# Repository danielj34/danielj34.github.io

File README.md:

# danielj34.github.io
Daniel Joseph — engineering portfolio

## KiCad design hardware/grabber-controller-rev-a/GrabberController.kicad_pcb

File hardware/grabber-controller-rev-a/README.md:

# Grabber Controller - Revision A

ESP32 motor-control carrier PCB design, Revision A. November 12, 2026.

This design develops the ESP32 / dual-motor-controller concept for Daniel Joseph's assistive-grabber portfolio. The team's completed mechanical prototype used a switch-based control circuit. The files here document the PCB design.

## Design

- 111.76 x 86.36 mm two-layer carrier PCB, nominal 1.6 mm FR-4 / 1 oz copper.
- U1 is a socketed Espressif ESP32-DevKitC V4 with a WROOM module. The two 19-pin rows are 25.40 mm apart at 2.54 mm pin pitch. WROVER variants are unsuitable for the selected GPIO16/17 assignment.
- U2 is a socket for the SparkFun ROB-14450 dual TB6612FNG driver module, two 8-pin rows 15.24 mm apart at 2.54 mm pitch. The driver IC is on that module, not directly on this carrier.
- ESP32 logic power comes only through its own USB connector. The carrier's J1 input feeds only the motor rail. The two rails share ground.
- J1 is a nominal 6-12 V motor input. F1 is a resettable fuse footprint. C1 is 220 uF / 25 V bulk decoupling; C2 and C3 are 100 nF ceramic bypass capacitors.
- J2 and J3 are the two brushed-DC motor outputs.
- J4 exposes GND, OPEN, CLOSE and STOP inputs for normally-open switches. R1-R3 pull the inputs up to 3.3 V.
- J5 is a removable enable shunt. U1 drives ENABLE_REQUEST, and R4 holds driver STBY low if the link is absent. This is a bench enable feature, not a certified emergency-stop circuit.
- J6 is a logic-rail measurement header, not a power input.
- Nominal signal widths are 0.30 mm, logic/ground routing 0.50 mm, and motor-supply/output routing 1.00 mm. The router used a 0.23 mm clearance allowance; the supplied native DRC report uses the editor's default constraints.

## Altium Designer

`GrabberController_AltiumImport.PCB` is an editable P-CAD ASCII interchange file. Altium Designer supports importing this format through File > Import Wizard > P-CAD Designs and Libraries Files. The wizard creates a native Altium PCB project and PcbDoc.

Map Top and Bottom to the two signal layers and BOARD to the board-outline/mechanical layer. Review the mechanical outline and recreate the native board shape after import if required. Reapply constraints and run Altium's own DRC before treating the imported file as an Altium design release.

The design was authored and checked through a PCB design library and KiCad 9.0.7, not through the Altium application. The portfolio layout illustration uses the actual copper geometry in a red/blue EDA colour scheme. Native Altium opening and DRC have not been verified.

## Files

- `GrabberController_AltiumImport.PCB` - P-CAD ASCII layout, including components, pads, nets, tracks, vias, outline and layer information.
- `GrabberController.kicad_pcb` - editable native board used for geometry/DRC verification.
- `BOM.csv` - component values and footprint assumptions.
- `PinConnections.csv` - authoritative point-to-point net assignment table, including unused pins.
- `Connections.svg` - net-labelled connection schematic generated from the same pin table. Matching labels denote an electrical connection. It is a connection drawing, not a native Altium schematic document.
- `PCB_Layout.svg` - actual routing illustration.
- `board-data.json` - placement and copper geometry used for the illustration and interchange export.
- `drc.json` - native-board check report.
- `Validation.md` - check results and import-round-trip limits.

## Engineering assumptions and outstanding work

The initial design target is current-limited bench loads up to 0.5 A per motor channel. The TB6612FNG manufacturer's average/peak ratings are not interchangeable with a motor's stall current. The original JGB37 motor compatibility has not been established. Measure motor startup/stall current and review driver and fuse selection before using this circuit with those motors.

This layout has no current sensing, grip-force sensing, travel-limit inputs, reverse-polarity protection, or validated thermal/current-handling performance. The fuse does not regulate motor current. Host firmware must default the driver to standby, handle conflicting commands, enforce motion timeouts and validate the STOP input before bench use. No new firmware is supplied with this design.

Component body envelopes, actual connector and PTC part selection, pad/drill tolerances, module mounting orientation, antenna/RF clearance, enclosure clearances, EMC, bulk-capacitor sizing, and patient-use safety require review. The board is not a fabrication release or a tested assistive device.

## Primary references

- Espressif DevKitC V4 pinout and power options: https://docs.espressif.com/projects/esp-dev-kits/en/latest/esp32/esp32-devkitc/user_guide.html
- Espressif mechanical dimensions: https://dl.espressif.com/dl/schematics/esp32_devkitc_v4_dimensions.pdf
- SparkFun ROB-14450 hardware: https://github.com/sparkfun/Motor_Driver-Dual_TB6612FNG
- Toshiba TB6612FNG datasheet: https://toshiba.semicon-storage.com/info/datasheet_en_20141001.pdf?did=10660
- Altium P-CAD import documentation: https://www.altium.com/documentation/altium-designer/design-tools-interfacing/altium-design-software-import-export

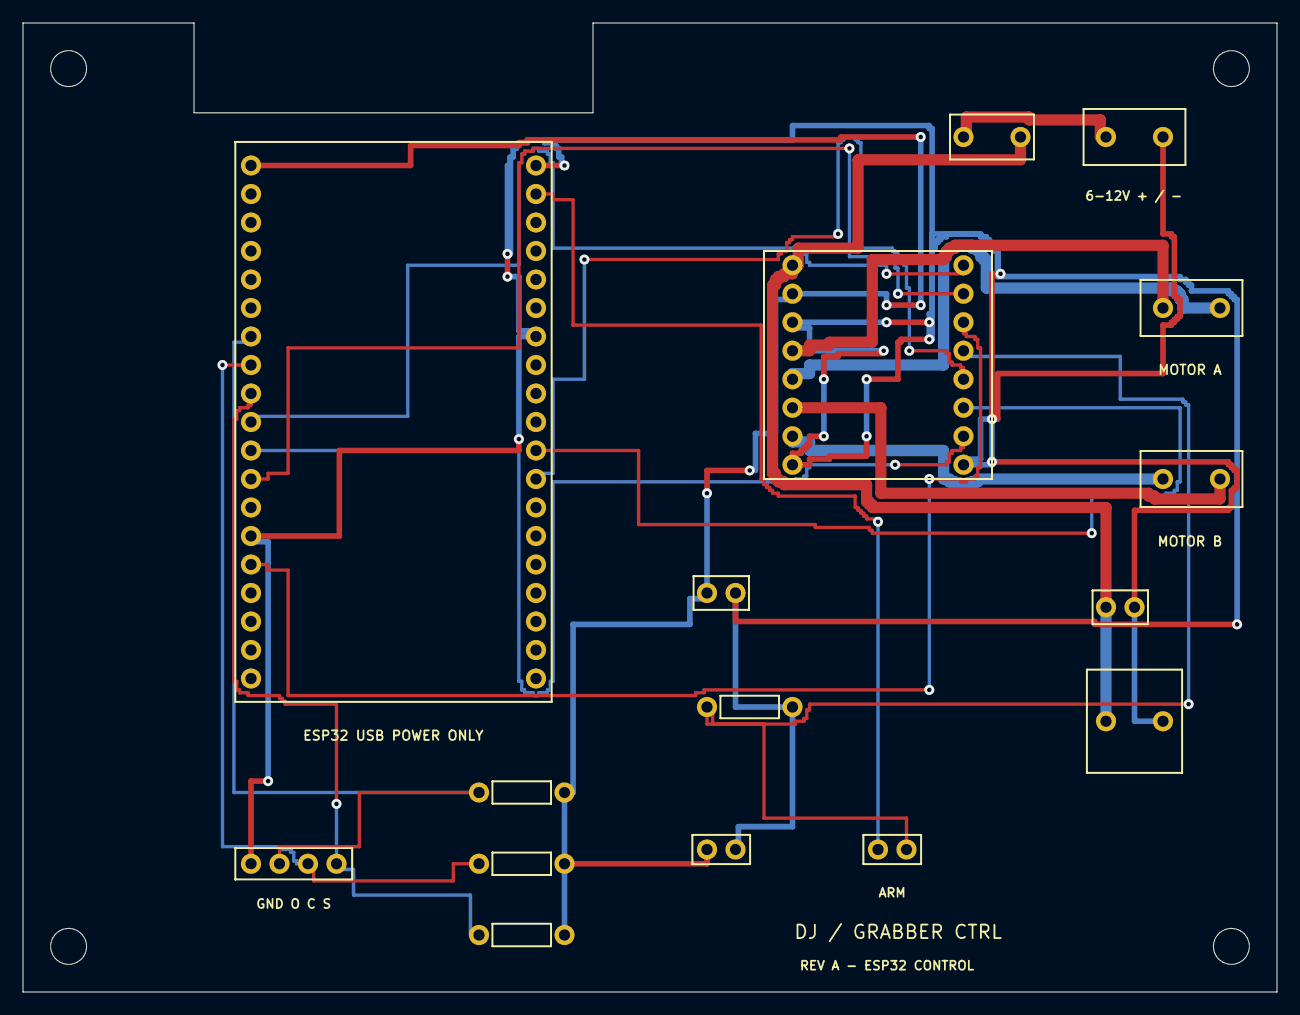
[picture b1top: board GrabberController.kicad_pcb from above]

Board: 2 copper layers, 111.8 x 86.4 mm, 20 parts (0 on the bottom side), 19 nets.

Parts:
C1: 220uF 25V
C2: 100nF 50V
C3: 100nF 16V
F1: 2A RESETTABLE FUSE
H1, H2, H3, H4: (no value)
J1: MOTOR POWER 6-12V
J2: MOTOR A
J3: MOTOR B
J4: OPEN / CLOSE / STOP
J5: ARM LINK
J6: 3V3 / GND TEST
R1, R2, R3: 10k
R4: 10k STANDBY PULLDOWN
U1: ESP32-DevKitC V4 / WROOM
U2: SparkFun TB6612FNG ROB-14450

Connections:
3V3: C3.1, J6.1, R1.2, R2.2, R3.2, U1.1, U2.2
AIN1: U1.15, U2.14
AIN2: U1.12, U2.15
BIN1: U1.31, U2.12
BIN2: U1.30, U2.11
BTN_CLOSE: J4.3, R2.1, U1.8
BTN_OPEN: J4.2, R1.1, U1.7
BTN_STOP: J4.4, R3.1, U1.9
ENABLE_REQUEST: J5.1, U1.21
GND: C1.2, C2.2, C3.2, J1.2, J4.1, J6.2, R4.2, U1.14, U1.20, U1.26, U2.3, U2.8, U2.9
MA1: J2.1, U2.4
MA2: J2.2, U2.5
MB1: J3.1, U2.7
MB2: J3.2, U2.6
PWMA: U1.10, U2.16
PWMB: U1.11, U2.10
STBY: J5.2, R4.1, U2.13
VM: C1.1, C2.1, F1.2, U2.1
VM_RAW: F1.1, J1.1

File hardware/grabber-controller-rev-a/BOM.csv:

Reference,Value,Specification
U1,ESP32-DevKitC V4 / WROOM,Socketed development module; USB-powered; 2 x 19 pins; 25.4 mm row spacing
U2,SparkFun TB6612FNG ROB-14450,"Socketed dual motor-driver module, ROB-14450; 2 x 8 pins, 15.24 mm rows"
J1,MOTOR POWER 6-12V,"2-pin 5.08 mm terminal, >= 3 A / 25 V"
F1,2A RESETTABLE FUSE,"Radial PTC, 2 A hold; verify trip curve for selected loads"
J2,MOTOR A,"2-pin 5.08 mm terminal, >= 3 A / 25 V"
J3,MOTOR B,"2-pin 5.08 mm terminal, >= 3 A / 25 V"
C1,220uF 25V,Radial polarized electrolytic; 5.08 mm pitch; 10 mm maximum diameter
C2,100nF 50V,Radial ceramic X7R; 2.54 mm pitch
C3,100nF 16V,Radial ceramic X7R; logic-rail bypass; 2.54 mm pitch
J4,OPEN / CLOSE / STOP,1 x 4 header; external normally-open dry-contact switches to GND
R1,10k,"Axial 10 kOhm, 1%, 0.25 W; 7.62 mm pitch"
R2,10k,"Axial 10 kOhm, 1%, 0.25 W; 7.62 mm pitch"
R3,10k,"Axial 10 kOhm, 1%, 0.25 W; 7.62 mm pitch"
R4,10k STANDBY PULLDOWN,"Axial 10 kOhm, 1%, 0.25 W; driver disabled when enable link is open"
J5,ARM LINK,1 x 2 header and removable shunt; open link forces standby
J6,3V3 / GND TEST,1 x 2 2.54 mm test header; measurement only
